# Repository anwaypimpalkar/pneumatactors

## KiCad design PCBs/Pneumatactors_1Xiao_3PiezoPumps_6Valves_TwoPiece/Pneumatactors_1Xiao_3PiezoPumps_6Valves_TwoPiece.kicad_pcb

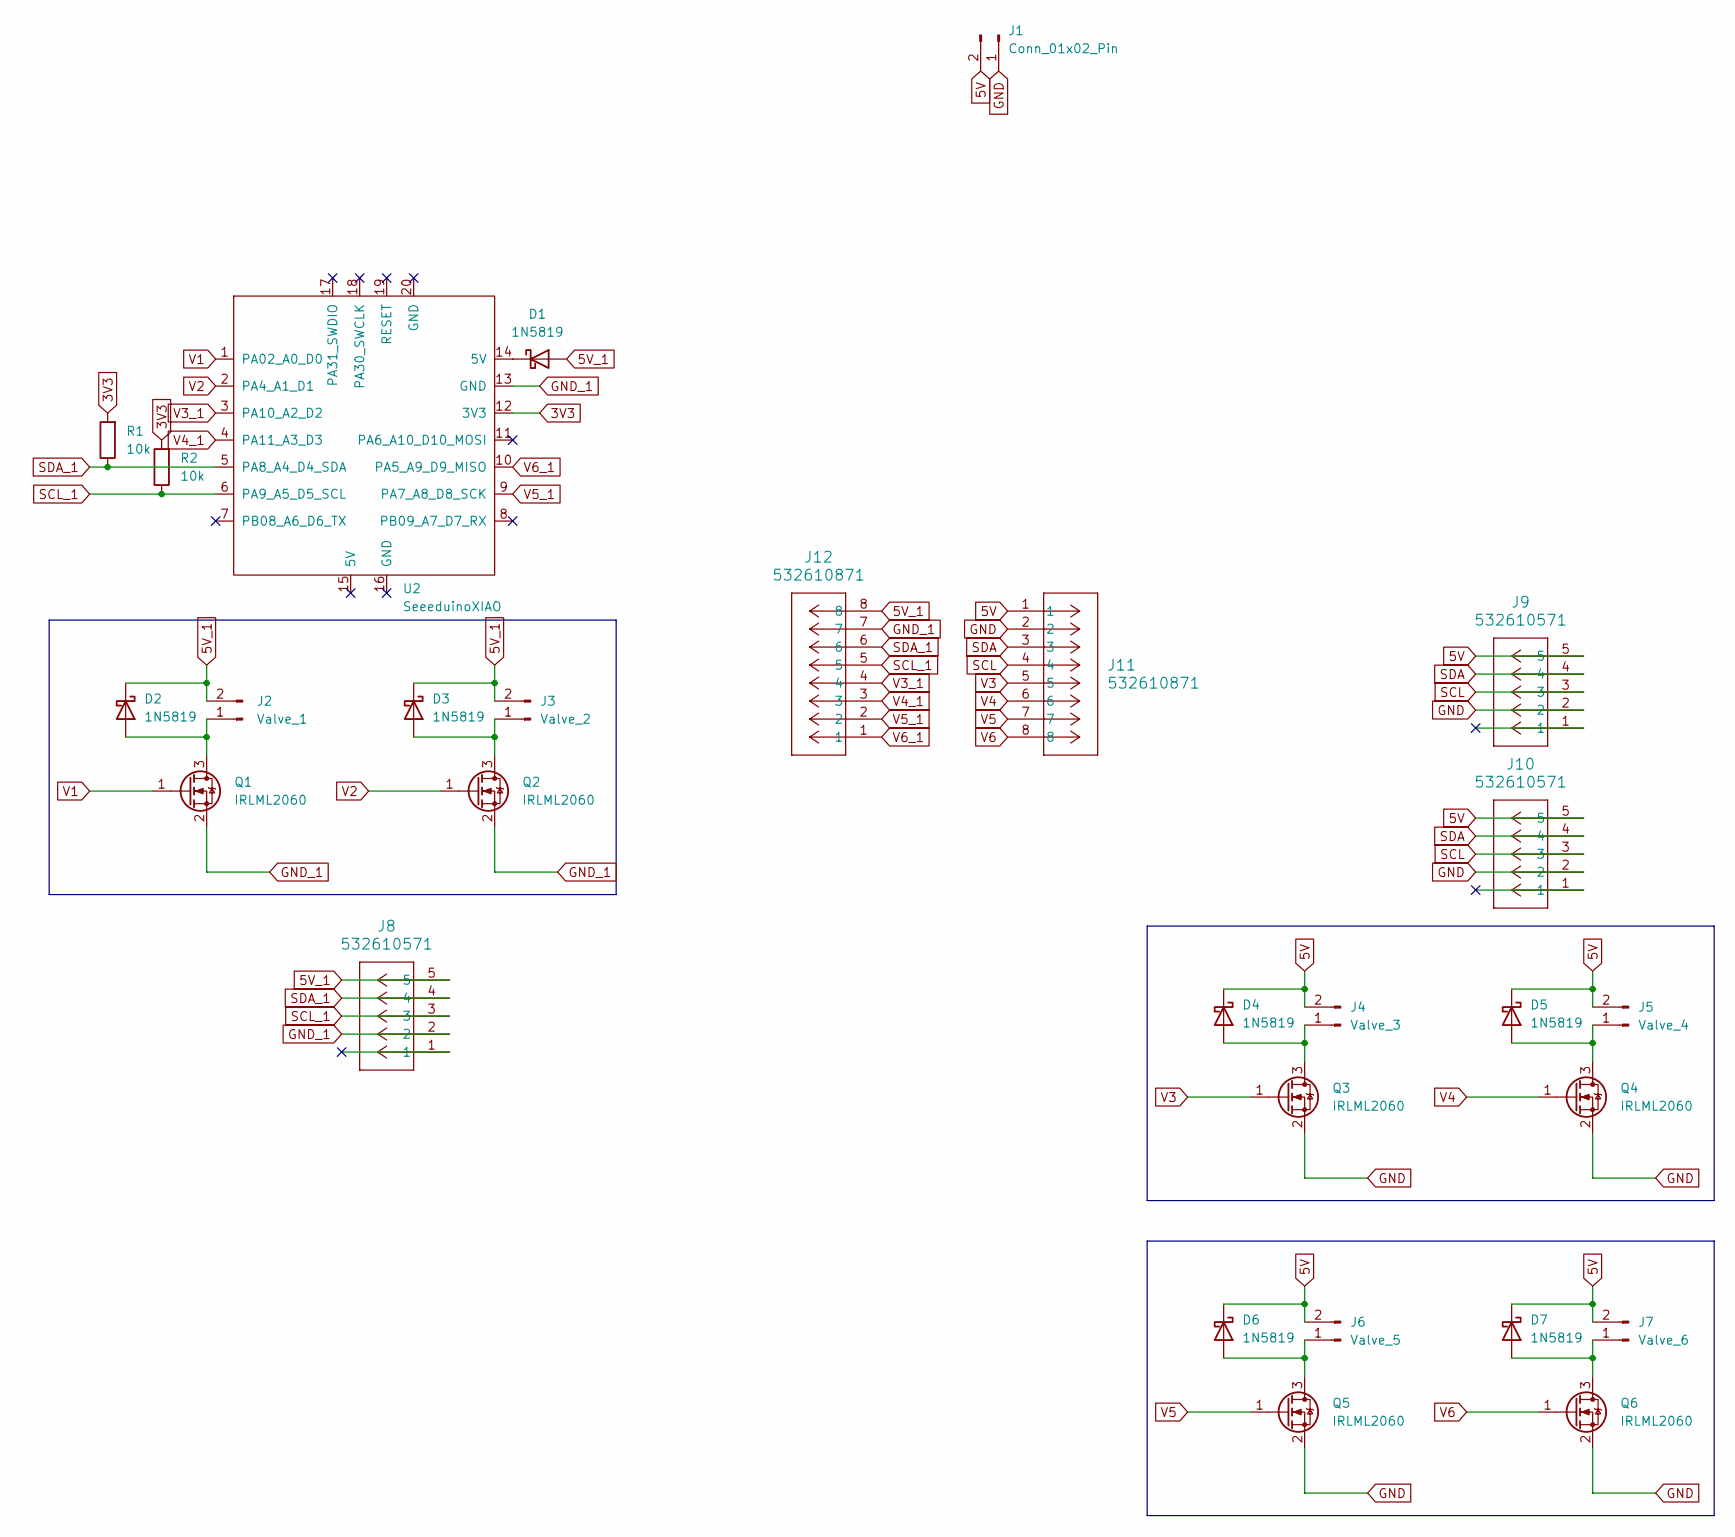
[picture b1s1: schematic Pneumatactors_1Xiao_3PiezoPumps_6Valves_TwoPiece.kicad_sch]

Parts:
D1, D2, D3, D4, D5, D6, D7: 1N5819; D_SMA
J1: Conn_01x02_Pin; PinHeader_1x02_P2.54mm_Vertical
J2: Valve_1; CONN02_533984002_MOL
J3: Valve_2; CONN02_533984002_MOL
J4: Valve_3; CONN02_533984002_MOL
J5: Valve_4; CONN02_533984002_MOL
J6: Valve_5; CONN02_533984002_MOL
J7: Valve_6; CONN02_533984002_MOL
J8, J9, J10: 532610571; CONN_532610001-SD_05_MOL
J11, J12: 532610871; CONN08_533980871_MOL
Q1, Q2, Q3, Q4, Q5, Q6: IRLML2060; SOT-23
R1, R2: 10k; R_1206_3216Metric_Pad1.30x1.75mm_HandSolder
U2: SeeeduinoXIAO; XIAO-ESP32S3-SMD

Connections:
3V3: R1.2, R2.2, U2.12 (3V3)
5V: D4.1 (K), D5.1 (K), D6.1 (K), D7.1 (K), J1.2, J4.2, J5.2, J6.2, J7.2, J9.5, J10.5, J11.1
5V_1: D1.2 (A), D2.1 (K), D3.1 (K), J2.2, J3.2, J8.5, J12.8
GND: J1.1, J9.2, J10.2, J11.2, Q3.2 (S), Q4.2 (S), Q5.2 (S), Q6.2 (S)
GND_1: J8.2, J12.7, Q1.2 (S), Q2.2 (S), U2.13 (GND)
unnamed: D1.1 (K), U2.14 (5V)
unnamed: D2.2 (A), J2.1, Q1.3 (D)
unnamed: D3.2 (A), J3.1, Q2.3 (D)
unnamed: D4.2 (A), J4.1, Q3.3 (D)
unnamed: D5.2 (A), J5.1, Q4.3 (D)
unnamed: D6.2 (A), J6.1, Q5.3 (D)
unnamed: D7.2 (A), J7.1, Q6.3 (D)
SCL: J9.3, J10.3, J11.4
SCL_1: J8.3, J12.5, R2.1, U2.6 (PA9_A5_D5_SCL)
SDA: J9.4, J10.4, J11.3
SDA_1: J8.4, J12.6, R1.1, U2.5 (PA8_A4_D4_SDA)
V1: Q1.1 (G), U2.1 (PA02_A0_D0)
V2: Q2.1 (G), U2.2 (PA4_A1_D1)
V3: J11.5, Q3.1 (G)
V3_1: J12.4, U2.3 (PA10_A2_D2)
V4: J11.6, Q4.1 (G)
V4_1: J12.3, U2.4 (PA11_A3_D3)
V5: J11.7, Q5.1 (G)
V5_1: J12.2, U2.9 (PA7_A8_D8_SCK)
V6: J11.8, Q6.1 (G)
V6_1: J12.1, U2.10 (PA5_A9_D9_MISO)

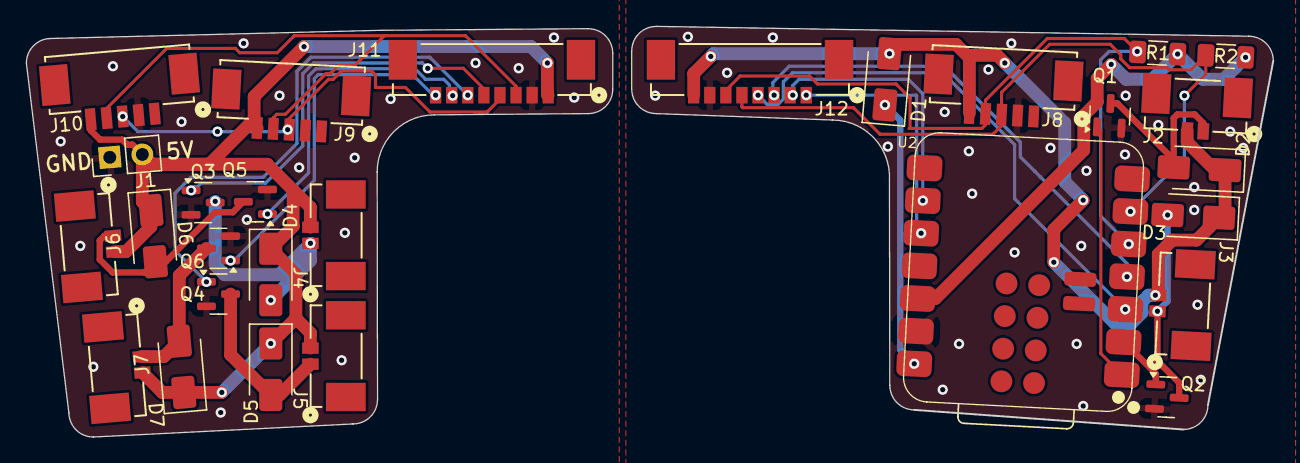
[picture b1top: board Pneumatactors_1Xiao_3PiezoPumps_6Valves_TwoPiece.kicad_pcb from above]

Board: 2 copper layers, 96.9 x 31.9 mm, 28 parts (0 on the bottom side), 26 nets.

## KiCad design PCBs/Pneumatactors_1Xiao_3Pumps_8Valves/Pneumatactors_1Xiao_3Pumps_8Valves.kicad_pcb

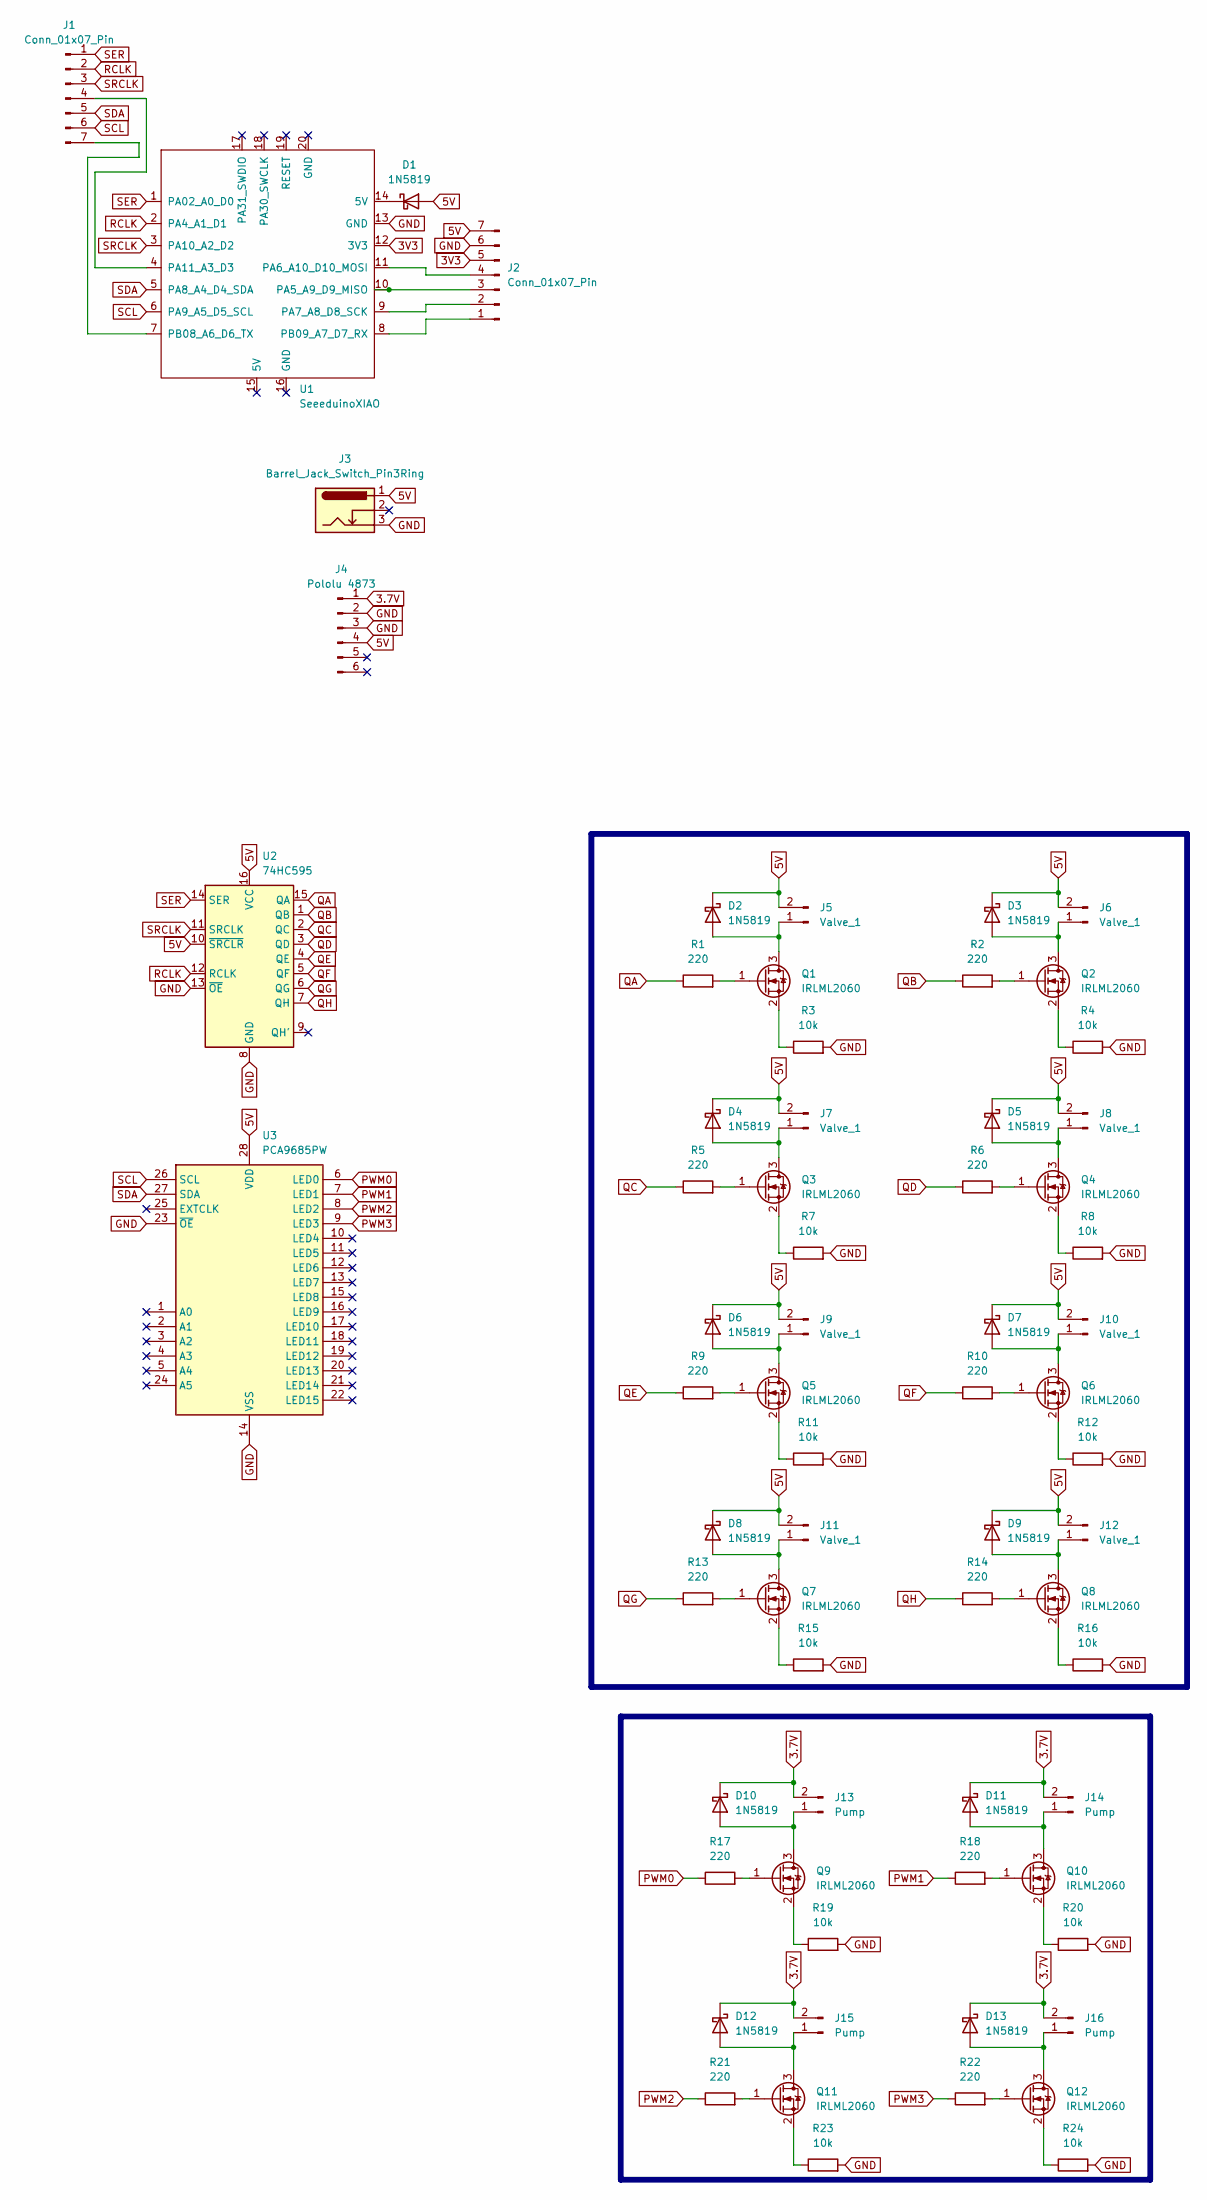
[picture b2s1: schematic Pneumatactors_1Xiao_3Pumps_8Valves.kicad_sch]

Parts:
D1, D2, D3, D4, D5, D6, D7, D8, D9, D10, D11, D12, D13: 1N5819; D_SMA
J1, J2: Conn_01x07_Pin; PinHeader_1x07_P2.54mm_Vertical
J3: Barrel_Jack_Switch_Pin3Ring; PJ-002A_CUD
J4: Pololu 4873; PinHeader_1x06_P2.54mm_Vertical
J5, J6, J7, J8, J9, J10, J11, J12: Valve_1; JST_PH_S2B-PH-SM4-TB_1x02-1MP_P2.00mm_Horizontal
J13, J14, J15, J16: Pump; JST_PH_S2B-PH-SM4-TB_1x02-1MP_P2.00mm_Horizontal
Q1, Q2, Q3, Q4, Q5, Q6, Q7, Q8, Q9, Q10, Q11, Q12: IRLML2060; SOT-23
R1, R2, R5, R6, R9, R10, R13, R14, R17, R18, R21, R22: 220; R_1206_3216Metric_Pad1.30x1.75mm_HandSolder
R3, R4, R7, R8, R11, R12, R15, R16, R19, R20, R23, R24: 10k; R_1206_3216Metric_Pad1.30x1.75mm_HandSolder
U1: SeeeduinoXIAO; XIAO-ESP32S3-SMD
U2: 74HC595; SSOP-16_5.3x6.2mm_P0.65mm
U3: PCA9685PW; TSSOP-28_4.4x9.7mm_P0.65mm

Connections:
3.7V: D10.1 (K), D11.1 (K), D12.1 (K), D13.1 (K), J4.1, J13.2, J14.2, J15.2, J16.2
3V3: J2.5, U1.12 (3V3)
5V: D1.2 (A), D2.1 (K), D3.1 (K), D4.1 (K), D5.1 (K), D6.1 (K), D7.1 (K), D8.1 (K), D9.1 (K), J2.7, J3.1, J4.4, J5.2, J6.2, J7.2, J8.2, J9.2, J10.2, J11.2, J12.2, U2.10 (~SRCLR), U2.16 (VCC), U3.28 (VDD)
GND: J2.6, J3.3, J4.2, J4.3, R3.2, R4.2, R7.2, R8.2, R11.2, R12.2, R15.2, R16.2, R19.2, R20.2, R23.2, R24.2, U1.13 (GND), U2.8 (GND), U2.13 (~OE), U3.14 (VSS), U3.23 (~OE)
unnamed: D1.1 (K), U1.14 (5V)
unnamed: D2.2 (A), J5.1, Q1.3 (D)
unnamed: D3.2 (A), J6.1, Q2.3 (D)
unnamed: D4.2 (A), J7.1, Q3.3 (D)
unnamed: D5.2 (A), J8.1, Q4.3 (D)
unnamed: D6.2 (A), J9.1, Q5.3 (D)
unnamed: D7.2 (A), J10.1, Q6.3 (D)
unnamed: D8.2 (A), J11.1, Q7.3 (D)
unnamed: D9.2 (A), J12.1, Q8.3 (D)
unnamed: D10.2 (A), J13.1, Q9.3 (D)
unnamed: D11.2 (A), J14.1, Q10.3 (D)
unnamed: D12.2 (A), J15.1, Q11.3 (D)
unnamed: D13.2 (A), J16.1, Q12.3 (D)
unnamed: J1.4, U1.4 (PA11_A3_D3)
unnamed: J1.7, U1.7 (PB08_A6_D6_TX)
unnamed: J2.1, U1.8 (PB09_A7_D7_RX)
unnamed: J2.2, U1.9 (PA7_A8_D8_SCK)
unnamed: J2.3, U1.10 (PA5_A9_D9_MISO)
unnamed: J2.4, U1.11 (PA6_A10_D10_MOSI)
unnamed: Q1.1 (G), R1.2
unnamed: Q1.2 (S), R3.1
unnamed: Q2.1 (G), R2.2
unnamed: Q2.2 (S), R4.1
unnamed: Q3.1 (G), R5.2
unnamed: Q3.2 (S), R7.1
unnamed: Q4.1 (G), R6.2
unnamed: Q4.2 (S), R8.1
unnamed: Q5.1 (G), R9.2
unnamed: Q5.2 (S), R11.1
unnamed: Q6.1 (G), R10.2
unnamed: Q6.2 (S), R12.1
unnamed: Q7.1 (G), R13.2
unnamed: Q7.2 (S), R15.1
unnamed: Q8.1 (G), R14.2
unnamed: Q8.2 (S), R16.1
unnamed: Q9.1 (G), R17.2
unnamed: Q9.2 (S), R19.1
unnamed: Q10.1 (G), R18.2
unnamed: Q10.2 (S), R20.1
unnamed: Q11.1 (G), R21.2
unnamed: Q11.2 (S), R23.1
unnamed: Q12.1 (G), R22.2
unnamed: Q12.2 (S), R24.1
PWM0: R17.1, U3.6 (LED0)
PWM1: R18.1, U3.7 (LED1)
PWM2: R21.1, U3.8 (LED2)
PWM3: R22.1, U3.9 (LED3)
QA: R1.1, U2.15 (QA)
QB: R2.1, U2.1 (QB)
QC: R5.1, U2.2 (QC)
QD: R6.1, U2.3 (QD)
QE: R9.1, U2.4 (QE)
QF: R10.1, U2.5 (QF)
QG: R13.1, U2.6 (QG)
QH: R14.1, U2.7 (QH)
RCLK: J1.2, U1.2 (PA4_A1_D1), U2.12 (RCLK)
SCL: J1.6, U1.6 (PA9_A5_D5_SCL), U3.26 (SCL)
SDA: J1.5, U1.5 (PA8_A4_D4_SDA), U3.27 (SDA)
SER: J1.1, U1.1 (PA02_A0_D0), U2.14 (SER)
SRCLK: J1.3, U1.3 (PA10_A2_D2), U2.11 (SRCLK)

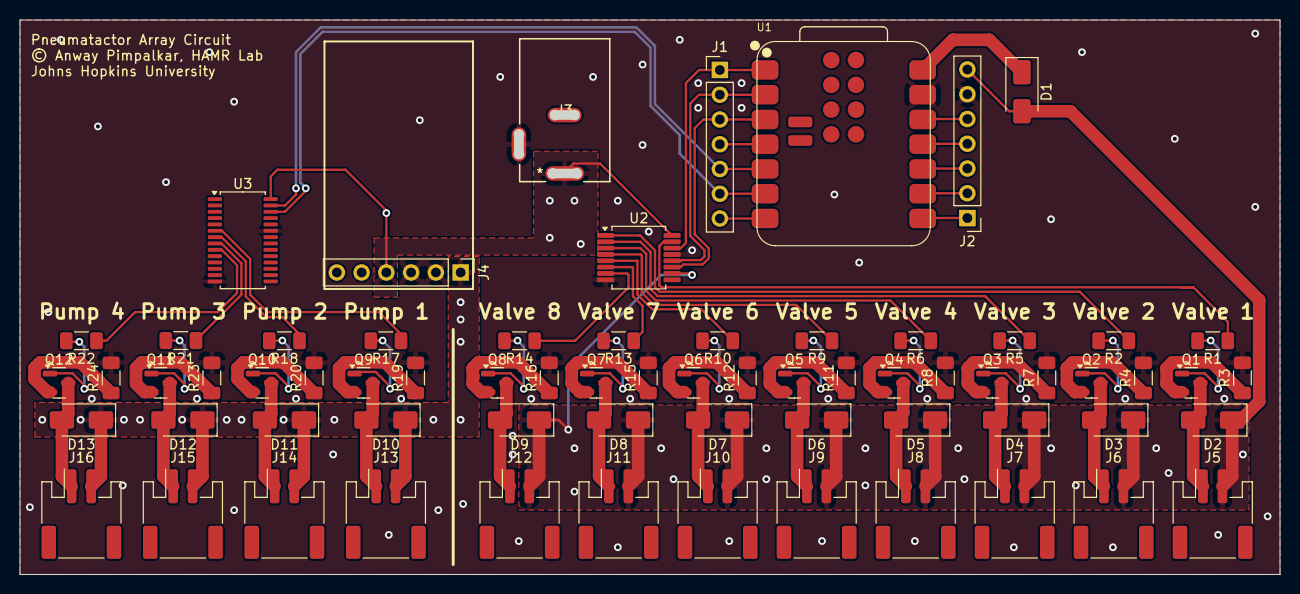
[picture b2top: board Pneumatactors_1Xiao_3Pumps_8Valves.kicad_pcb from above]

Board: 2 copper layers, 128.4 x 56.0 mm, 68 parts (0 on the bottom side), 64 nets.

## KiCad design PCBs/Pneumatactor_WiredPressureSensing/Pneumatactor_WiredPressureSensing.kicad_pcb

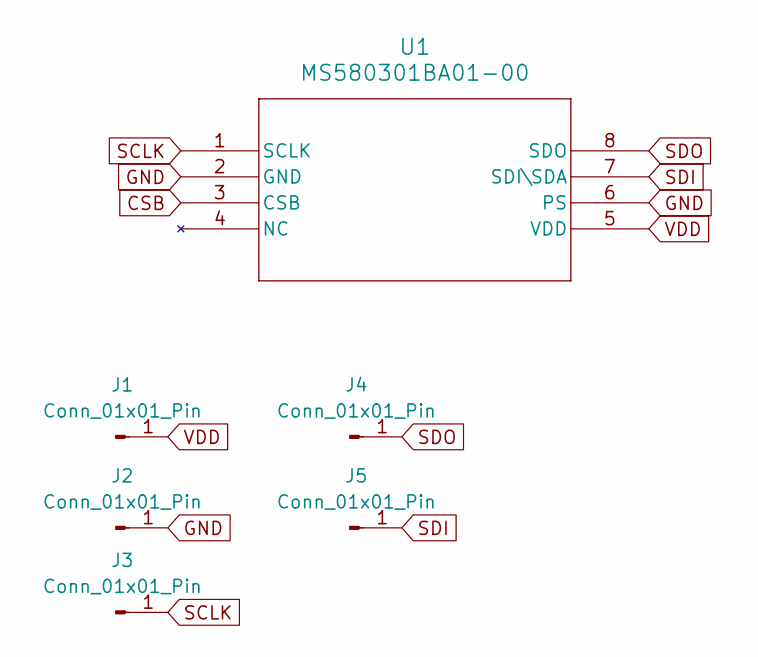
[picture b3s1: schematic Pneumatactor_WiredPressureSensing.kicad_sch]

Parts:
J1, J2, J3, J4, J5: Conn_01x01_Pin; SingleSMDPad
U1: MS580301BA01-00; MS5803-01BA01_TEC

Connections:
CSB: U1.3 (CSB)
GND: J2.1, U1.2 (GND), U1.6 (PS)
SCLK: J3.1, U1.1 (SCLK)
SDI: J5.1, U1.7 (SDI\SDA)
SDO: J4.1, U1.8 (SDO)
VDD: J1.1, U1.5 (VDD)

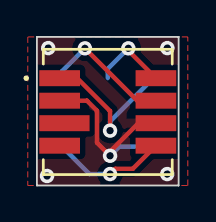
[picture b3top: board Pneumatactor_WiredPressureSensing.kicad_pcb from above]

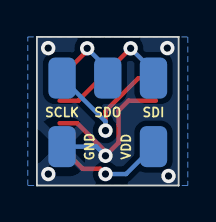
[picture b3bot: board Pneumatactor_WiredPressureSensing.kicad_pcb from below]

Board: 2 copper layers, 7.9 x 8.3 mm, 6 parts (5 on the bottom side), 5 nets.

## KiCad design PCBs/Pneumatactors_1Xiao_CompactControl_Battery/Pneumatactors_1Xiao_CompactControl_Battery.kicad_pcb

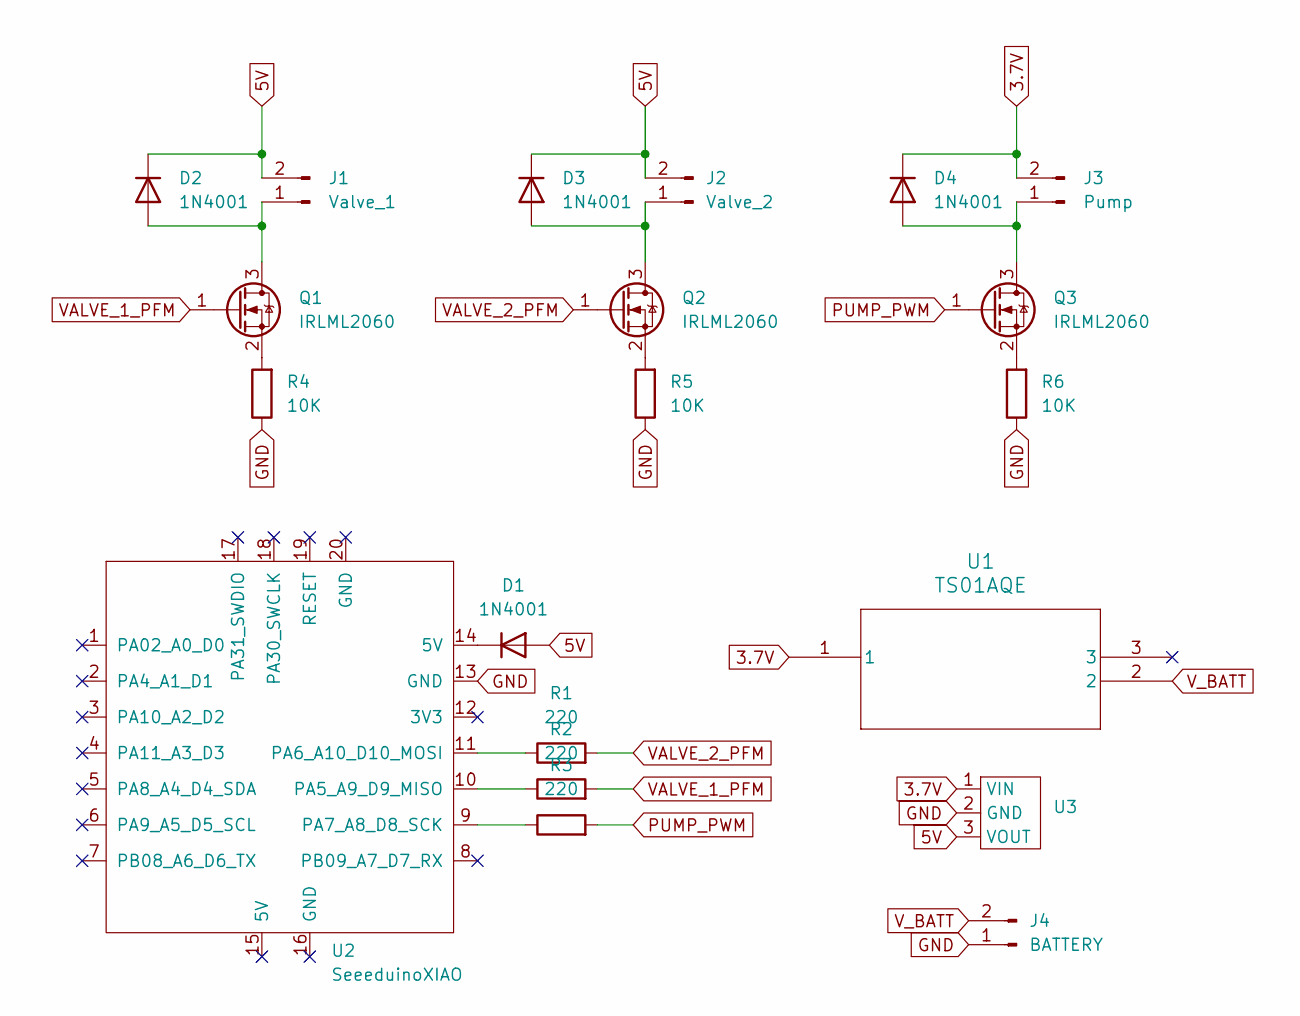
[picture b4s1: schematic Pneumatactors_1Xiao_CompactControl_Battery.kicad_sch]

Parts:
D1, D2, D3, D4: 1N4001; D_SOD-123F
J1: Valve_1; JST_PH_S2B-PH-SM4-TB_1x02-1MP_P2.00mm_Horizontal
J2: Valve_2; JST_PH_S2B-PH-SM4-TB_1x02-1MP_P2.00mm_Horizontal
J3: Pump; JST_PH_S2B-PH-SM4-TB_1x02-1MP_P2.00mm_Horizontal
J4: BATTERY; JST_PH_S2B-PH-SM4-TB_1x02-1MP_P2.00mm_Horizontal
Q1, Q2, Q3: IRLML2060; SOT-23
R1, R2, R3: 220; R_1206_3216Metric_Pad1.30x1.75mm_HandSolder
R4, R5, R6: 10K; R_1206_3216Metric_Pad1.30x1.75mm_HandSolder
U1: TS01AQE; SW3_TS01A
U2: SeeeduinoXIAO; XIAO-ESP32S3-SMD
U3: Pololu 2564 Step Up

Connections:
3.7V: D4.1 (K), J3.2, U1.1, U3.1 (VIN)
5V: D1.2 (A), D2.1 (K), D3.1 (K), J1.2, J2.2, U3.3 (VOUT)
GND: J4.1, R4.1, R5.1, R6.1, U2.13 (GND), U3.2 (GND)
unnamed: D1.1 (K), U2.14 (5V)
unnamed: D2.2 (A), J1.1, Q1.3 (D)
unnamed: D3.2 (A), J2.1, Q2.3 (D)
unnamed: D4.2 (A), J3.1, Q3.3 (D)
unnamed: Q1.2 (S), R4.2
unnamed: Q2.2 (S), R5.2
unnamed: Q3.2 (S), R6.2
unnamed: R2.1, U2.10 (PA5_A9_D9_MISO)
unnamed: R1.1, U2.11 (PA6_A10_D10_MOSI)
unnamed: R3.1, U2.9 (PA7_A8_D8_SCK)
PUMP_PWM: Q3.1 (G), R3.2
VALVE_1_PFM: Q1.1 (G), R2.2
VALVE_2_PFM: Q2.1 (G), R1.2
V_BATT: J4.2, U1.2

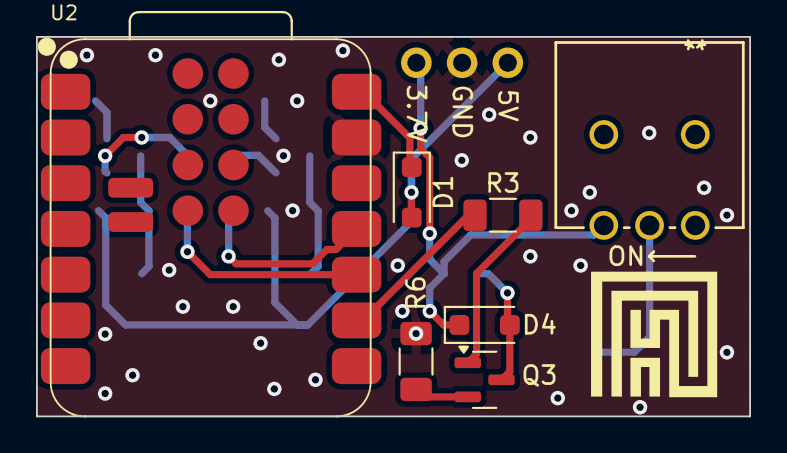
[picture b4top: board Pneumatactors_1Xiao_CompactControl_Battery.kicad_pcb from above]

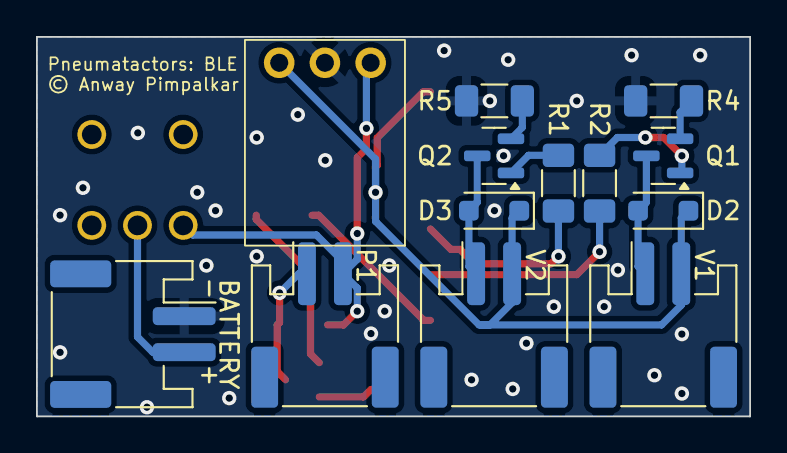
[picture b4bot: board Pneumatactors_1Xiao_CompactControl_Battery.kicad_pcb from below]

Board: 2 copper layers, 39.6 x 21.1 mm, 20 parts (13 on the bottom side), 17 nets.

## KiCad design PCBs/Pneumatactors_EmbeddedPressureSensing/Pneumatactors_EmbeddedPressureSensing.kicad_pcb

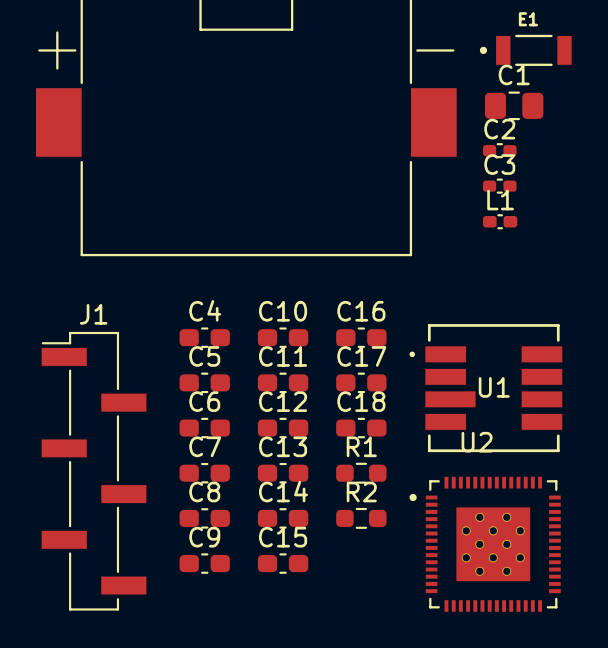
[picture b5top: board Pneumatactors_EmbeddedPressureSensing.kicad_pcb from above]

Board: 2 copper layers, 26 parts (0 on the bottom side), 19 nets, no tracks yet.

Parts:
BT1: BHSD-1225-SM; BAT_BHSD-1225-SM
C1: 100u; C_0805_2012Metric_Pad1.18x1.45mm_HandSolder
C2: 1p; C_0402_1005Metric_Pad0.74x0.62mm_HandSolder
C3: 0.8p; C_0402_1005Metric_Pad0.74x0.62mm_HandSolder
C4, C5, C7, C9, C11, C14, C17: 0.1u; C_0603_1608Metric_Pad1.08x0.95mm_HandSolder
C6: 10u; C_0603_1608Metric_Pad1.08x0.95mm_HandSolder
C8, C10, C12, C13, C15, C16, C18: 1u; C_0603_1608Metric_Pad1.08x0.95mm_HandSolder
E1: 2450AT18B100E; XDCR_2450AT18B100E
J1: Conn_01x06_Pin; PinHeader_1x06_P2.54mm_Vertical_SMD_Pin1Left
L1: 3.9n; L_0402_1005Metric_Pad0.77x0.64mm_HandSolder
R1, R2: 10k; R_0603_1608Metric_Pad0.98x0.95mm_HandSolder
U1: MS580301BA01-00; MS5803-01BA01_TEC
U2: ESP32-S3; IC_ESP32-S3

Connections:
CHIP_PU: BT1.-, C1.1, C4.1, C5.1, C7.1, C9.1, C11.1, C12.1, C14.1, C15.1, C17.1, C18.1, J1.4, U1.2 (GND), U1.6 (PS), U2.4 (CHIP_PU), U2.5 (GPIO0), U2.57 (GND)
CSB: U1.3 (CSB), U2.10 (GPIO5)
LNA_IN: C2.1, U2.1 (LNA_IN)
unnamed: C2.2, L1.1
unnamed: C3.1, L1.2
unnamed: C3.2, E1.1
unnamed: C6.1, C7.2
unnamed: C8.1, C9.2
unnamed: C10.1, C11.2
unnamed: C13.1, C14.2
unnamed: C16.1, C17.2
unnamed: C4.2, J1.5, R1.1
unnamed: C5.2, J1.6, R2.1
SCLK: U1.1 (SCLK), U2.33 (SPICLK)
SDI: U1.7 (SDI\SDA), U2.35 (SPID)
SDO: U1.8 (SDO), U2.34 (SPIQ)
U0RXD: J1.3, U2.50 (U0RXD)
U0TXD: J1.2, U2.49 (U0TXD)
VDD: BT1.+, C1.2, C6.2, C8.2, C10.2, C12.2, C13.2, C15.2, C16.2, C18.2, J1.1, R1.2, R2.2, U1.5 (VDD), U2.2 (VDD3P3), U2.3 (VDD3P3__1), U2.20 (VDD3P3_RTC), U2.29 (VDD_SPI), U2.46 (VDD3P3_CPU), U2.55 (VDDA1), U2.56 (VDDA2)

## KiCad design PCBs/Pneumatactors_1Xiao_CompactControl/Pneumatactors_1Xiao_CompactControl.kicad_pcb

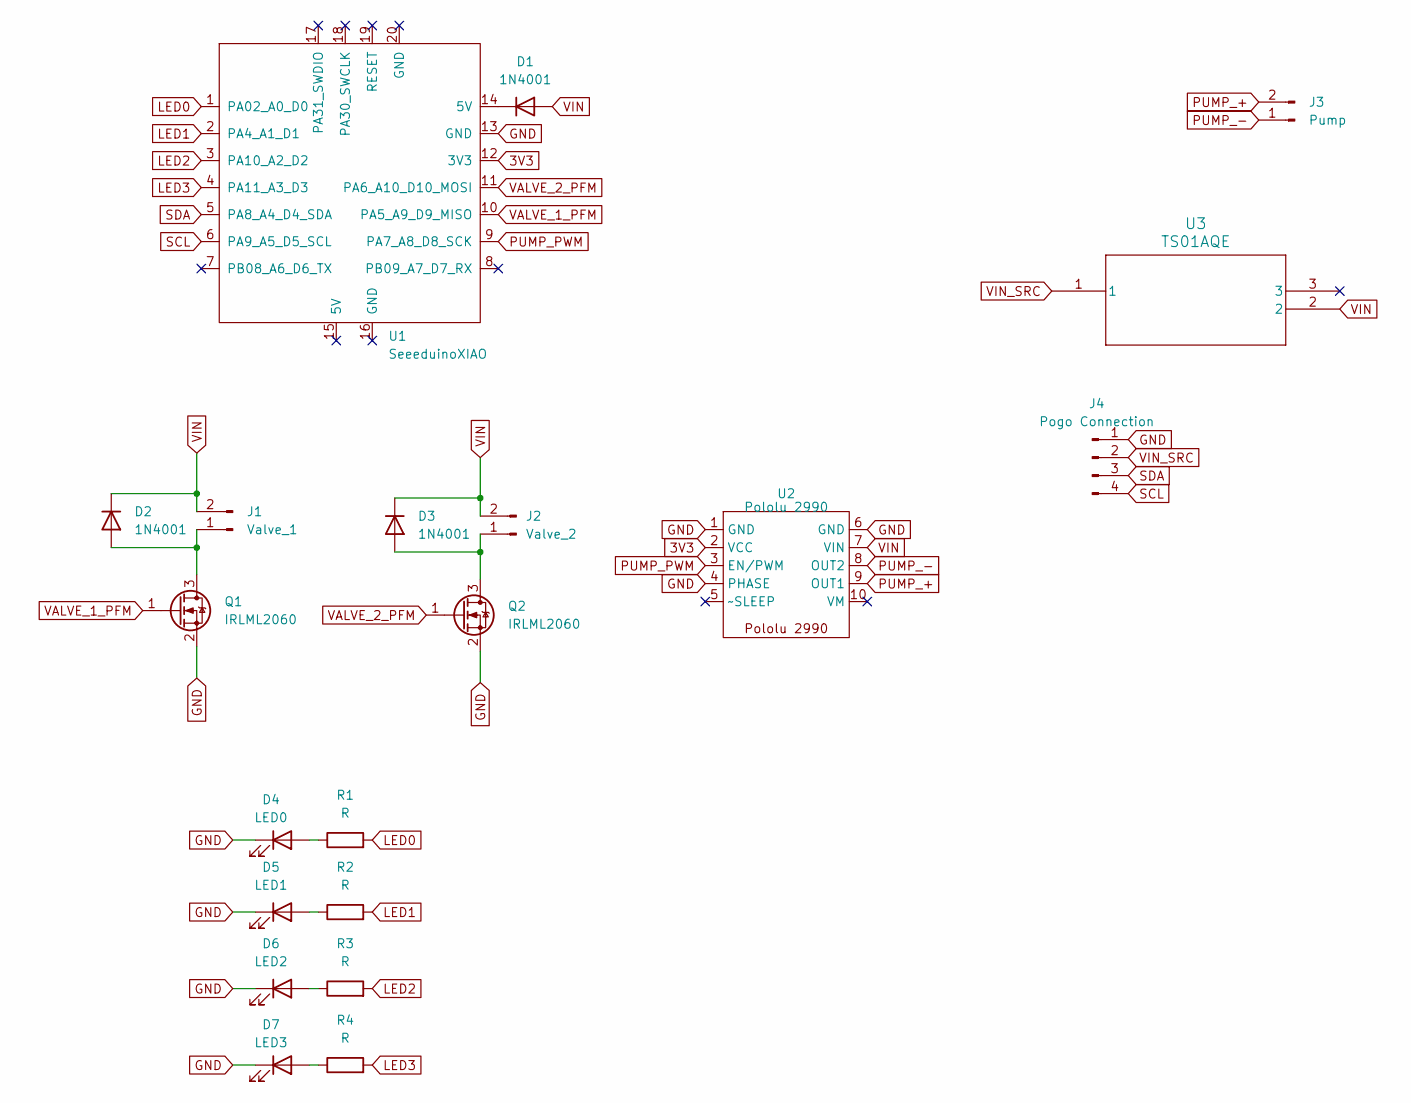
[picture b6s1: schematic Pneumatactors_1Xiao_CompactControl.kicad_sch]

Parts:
D1, D2, D3: 1N4001; D_SOD-123F
D4: LED0; LED_0201_0603Metric_Pad0.64x0.40mm_HandSolder
D5: LED1; LED_0201_0603Metric_Pad0.64x0.40mm_HandSolder
D6: LED2; LED_0201_0603Metric_Pad0.64x0.40mm_HandSolder
D7: LED3; LED_0201_0603Metric_Pad0.64x0.40mm_HandSolder
J1: Valve_1; PinHeader_1x02_P2.54mm_Vertical
J2: Valve_2; PinHeader_1x02_P2.54mm_Vertical
J3: Pump; PinHeader_1x02_P2.54mm_Vertical
J4: Pogo Connection; PinHeader_1x04_P2.54mm_Vertical
Q1, Q2: IRLML2060; SOT-23
R1, R2, R3, R4: R; R_0201_0603Metric_Pad0.64x0.40mm_HandSolder
U1: SeeeduinoXIAO; XIAO-Generic-Thruhole-14P-2.54-21X17.8MM
U2: Pololu 2990; Pololu 2990 Motor Driver
U3: TS01AQE; SW3_TS01A

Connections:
3V3: U1.12 (3V3), U2.2 (VCC)
GND: D4.1 (K), D5.1 (K), D6.1 (K), D7.1 (K), J4.1, Q1.2 (S), Q2.2 (S), U1.13 (GND), U2.1 (GND), U2.4 (PHASE), U2.6 (GND)
LED0: R1.2, U1.1 (PA02_A0_D0)
LED1: R2.2, U1.2 (PA4_A1_D1)
LED2: R3.2, U1.3 (PA10_A2_D2)
LED3: R4.2, U1.4 (PA11_A3_D3)
unnamed: D1.1 (K), U1.14 (5V)
unnamed: D2.2 (A), J1.1, Q1.3 (D)
unnamed: D3.2 (A), J2.1, Q2.3 (D)
unnamed: D4.2 (A), R1.1
unnamed: D5.2 (A), R2.1
unnamed: D6.2 (A), R3.1
unnamed: D7.2 (A), R4.1
PUMP_+: J3.2, U2.9 (OUT1)
PUMP_-: J3.1, U2.8 (OUT2)
PUMP_PWM: U1.9 (PA7_A8_D8_SCK), U2.3 (EN/PWM)
SCL: J4.4, U1.6 (PA9_A5_D5_SCL)
SDA: J4.3, U1.5 (PA8_A4_D4_SDA)
VALVE_1_PFM: Q1.1 (G), U1.10 (PA5_A9_D9_MISO)
VALVE_2_PFM: Q2.1 (G), U1.11 (PA6_A10_D10_MOSI)
VIN: D1.2 (A), D2.1 (K), D3.1 (K), J1.2, J2.2, U2.7 (VIN), U3.2
VIN_SRC: J4.2, U3.1

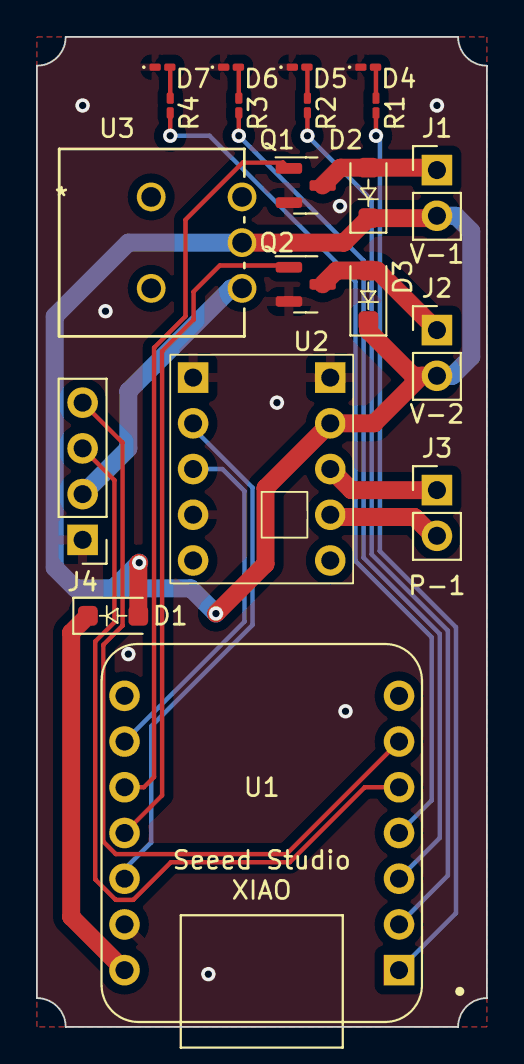
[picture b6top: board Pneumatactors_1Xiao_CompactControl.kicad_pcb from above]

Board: 2 copper layers, 25.0 x 55.0 mm, 20 parts (0 on the bottom side), 22 nets.

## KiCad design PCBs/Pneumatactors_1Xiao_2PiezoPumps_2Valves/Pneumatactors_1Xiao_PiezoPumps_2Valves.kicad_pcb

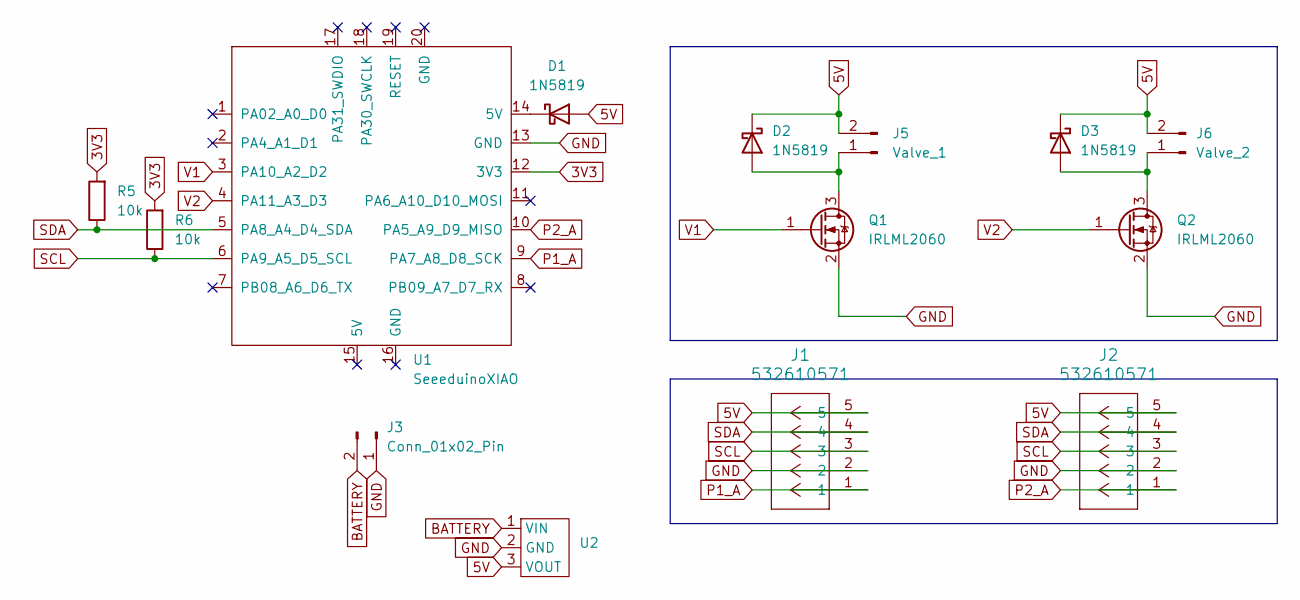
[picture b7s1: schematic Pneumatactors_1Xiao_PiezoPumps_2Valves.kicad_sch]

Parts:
D1, D2, D3: 1N5819; D_SMA
J1, J2: 532610571; CONN_532610001-SD_05_MOL
J3: Conn_01x02_Pin; JST_PH_S2B-PH-SM4-TB_1x02-1MP_P2.00mm_Horizontal
J5: Valve_1; CONN_532610001-SD_02_MOL
J6: Valve_2; CONN_532610001-SD_02_MOL
Q1, Q2: IRLML2060; SOT-23
R5, R6: 10k; R_1206_3216Metric_Pad1.30x1.75mm_HandSolder
U1: SeeeduinoXIAO; XIAO-ESP32S3-SMD
U2: Pololu 2564 Step Up

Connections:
3V3: R5.2, R6.2, U1.12 (3V3)
5V: D1.2 (A), D2.1 (K), D3.1 (K), J1.5, J2.5, J5.2, J6.2, U2.3 (VOUT)
BATTERY: J3.2, U2.1 (VIN)
GND: J1.2, J2.2, J3.1, Q1.2 (S), Q2.2 (S), U1.13 (GND), U2.2 (GND)
unnamed: D1.1 (K), U1.14 (5V)
unnamed: D2.2 (A), J5.1, Q1.3 (D)
unnamed: D3.2 (A), J6.1, Q2.3 (D)
P1_A: J1.1, U1.9 (PA7_A8_D8_SCK)
P2_A: J2.1, U1.10 (PA5_A9_D9_MISO)
SCL: J1.3, J2.3, R6.1, U1.6 (PA9_A5_D5_SCL)
SDA: J1.4, J2.4, R5.1, U1.5 (PA8_A4_D4_SDA)
V1: Q1.1 (G), U1.3 (PA10_A2_D2)
V2: Q2.1 (G), U1.4 (PA11_A3_D3)

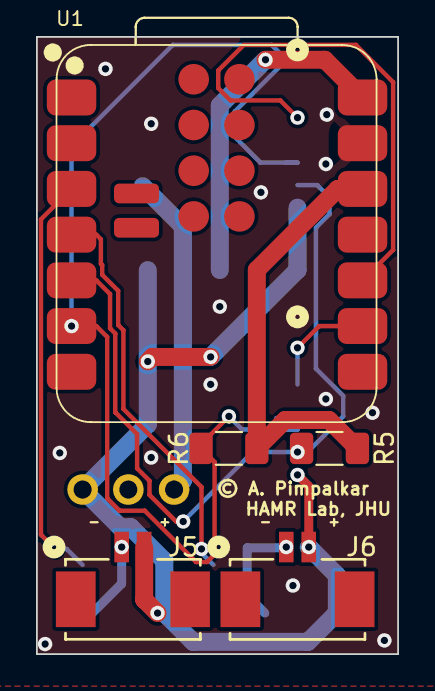
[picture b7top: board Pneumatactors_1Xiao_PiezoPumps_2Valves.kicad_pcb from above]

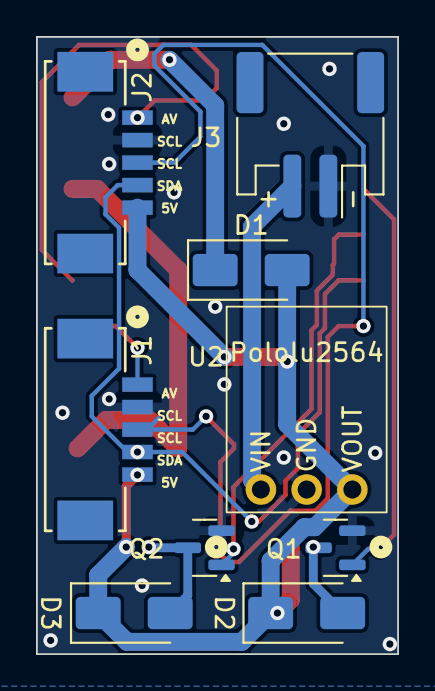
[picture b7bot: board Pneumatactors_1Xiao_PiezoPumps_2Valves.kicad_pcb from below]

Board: 2 copper layers, 20.1 x 34.3 mm, 14 parts (9 on the bottom side), 13 nets.

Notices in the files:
PCBs/Pneumatactors_1Xiao_2PiezoPumps_2Valves/Pneumatactors_1Xiao_PiezoPumps_2Valves.kicad_pcb:
© A. Pimpalkar
PCBs/Pneumatactors_1Xiao_3PiezoPumps_6Valves_TwoPiece/Pneumatactors_1Xiao_3PiezoPumps_6Valves_TwoPiece.kicad_pcb:
© Anway Pimpalkar
PCBs/Pneumatactors_1Xiao_3Pumps_8Valves/Pneumatactors_1Xiao_3Pumps_8Valves.kicad_pcb:
© Anway Pimpalkar, HAMR Lab
PCBs/Pneumatactors_1Xiao_CompactControl/Pneumatactors_1Xiao_CompactControl.kicad_pcb:
© Anway Pimpalkar 2025
